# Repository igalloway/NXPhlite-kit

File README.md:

# NXPhlite-kit

*** Update - The NXPhlite kit is being made available through NXP. The ECAD files have moved to Atium and the files here are well out of date. I will leave them here for reference. Please contact NXP and ask for NXPhlite Drones and Rovers reference design information. 

This is the EAGLE-PCB based hardware board files for the initial 'lite' kit for a UAV/Multicopter.
This is Opensource hardware, using NXP Kinetis K64 and other NXP devices.

The project currently defines:
* NXPhlite-PX4 - A Flight controller board which will run PX4 software.(Similar to PIXHAWK) 
* NXPESC-UF1 - An ESC for UAVs with Field oriented Control based off NXP Kinetis KV31 or KV11.
  * Note1: We will use KV31 until KV11 is gains KMS (Kinetis Motor Suite) software support. 
  * Nate2: KV31 does not have CAN-bus but will use use similar pins as KV11. 

<br><br>

* Note that the directory <bold>NXP-Eagle-7.5.0</bold> is the EAGLE PCB directory structure. You do not have to replace your exiting EAGLE structure, but can simply add these NEW directories under "Eagle Control Panel" <options><directories>

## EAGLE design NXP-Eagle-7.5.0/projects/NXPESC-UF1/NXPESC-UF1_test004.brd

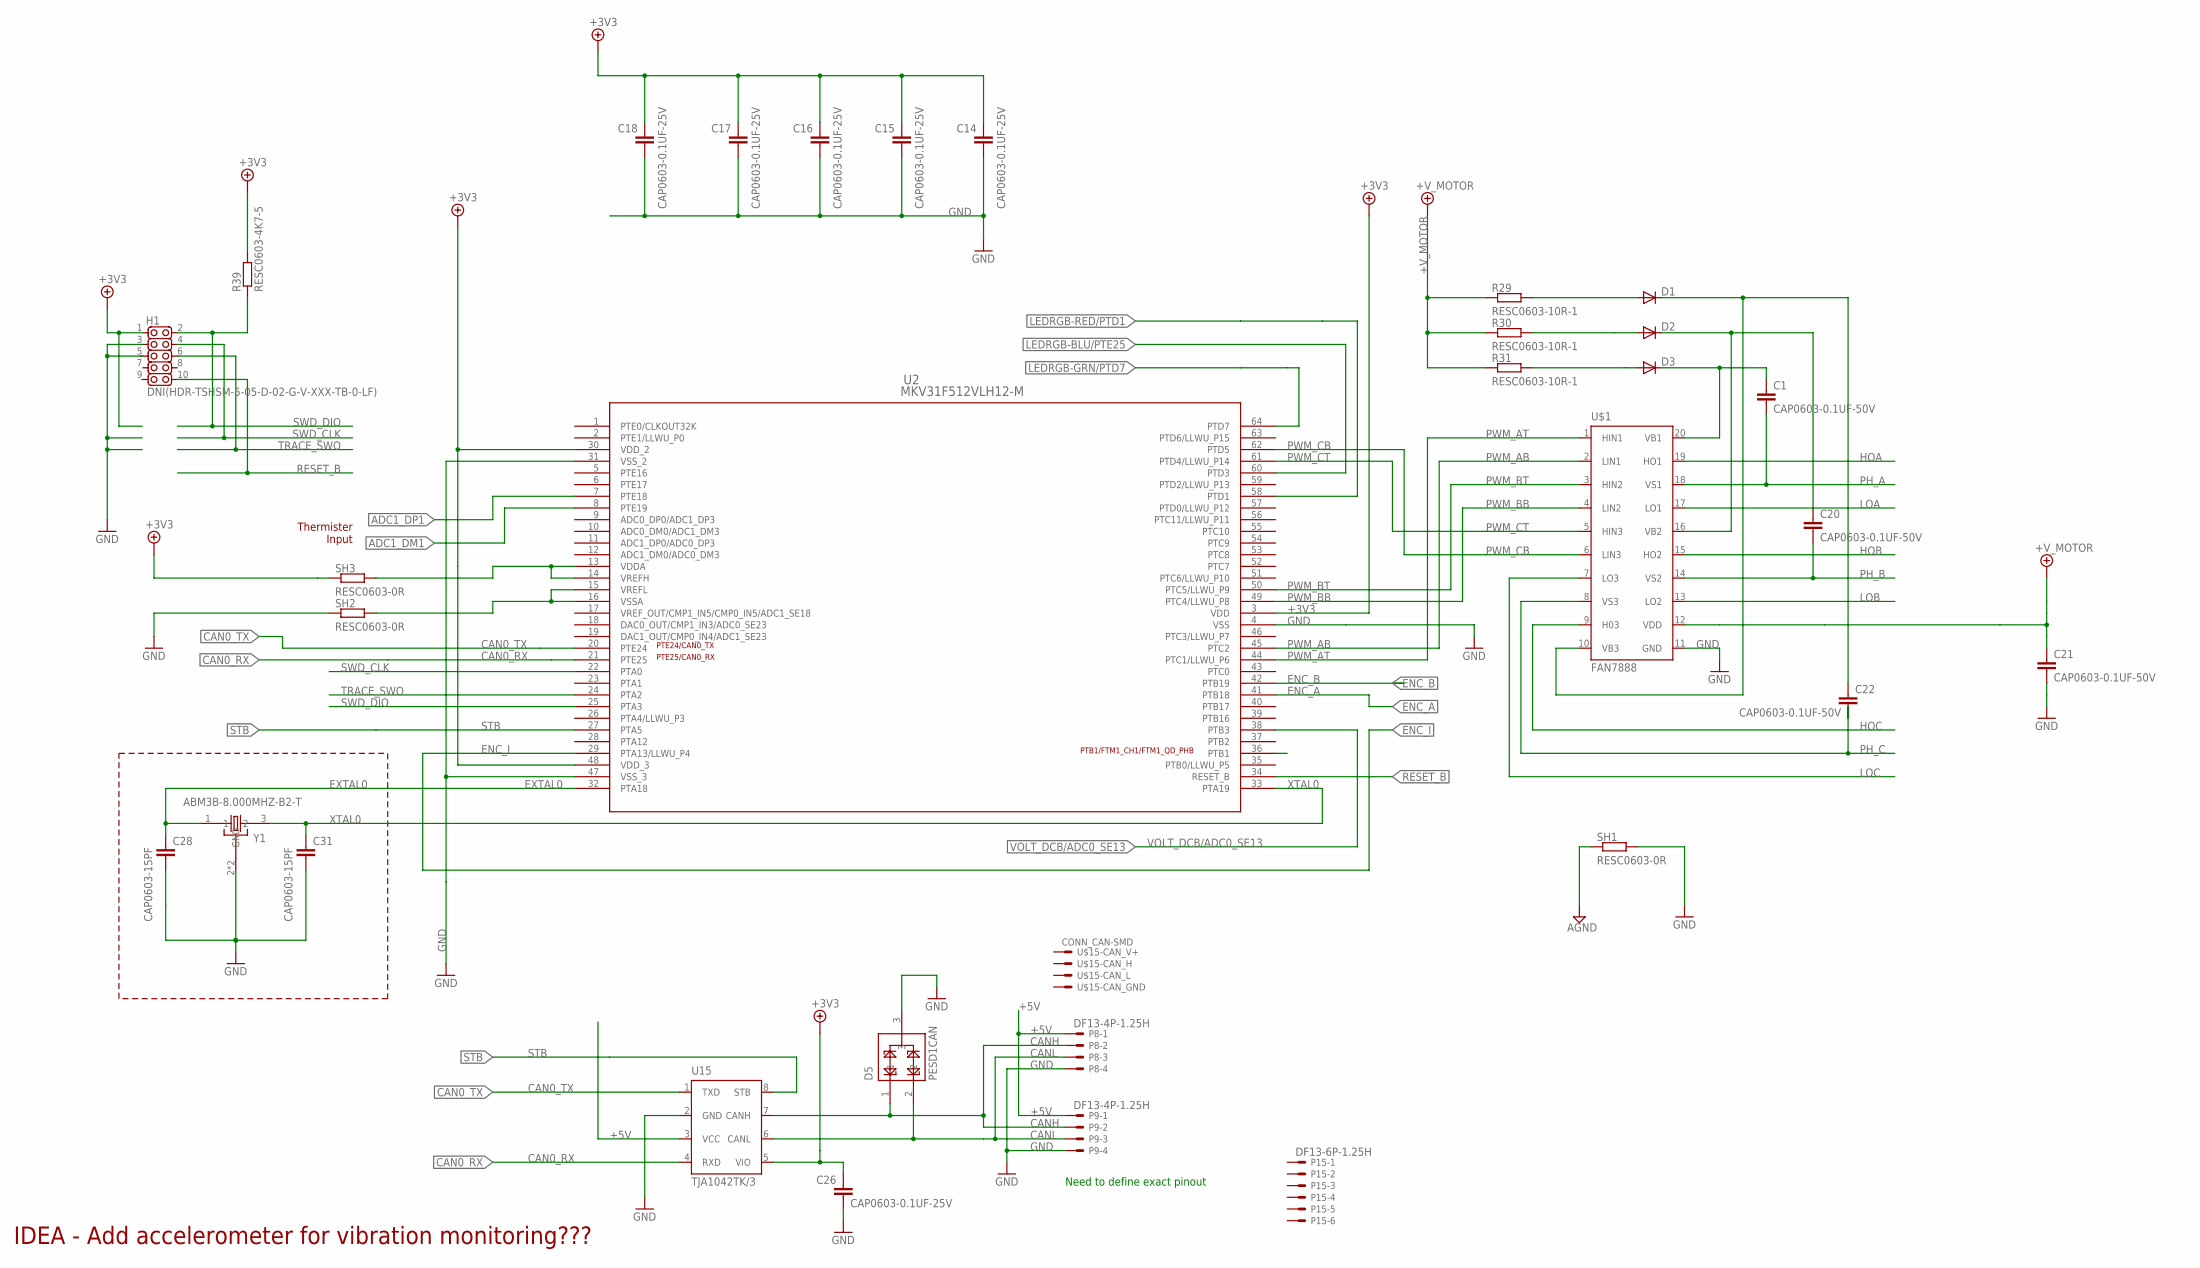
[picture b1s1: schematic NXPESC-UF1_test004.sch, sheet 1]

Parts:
C1, C20, C21, C22: CAP0603-0.1UF-50V; C0603
C14, C15, C16, C17, C18, C26: CAP0603-0.1UF-25V; C0603
C28, C31: CAP0603-15PF; C0603
D1, D2, D3: DIODE-SOD323-R; SOD323-R
D5: PESD1CAN; SOT23-3
H1: DNI(HDR-TSHSM-5-05-D-02-G-V-XXX-TB-0-LF); HD2X5-SMD-0.05"
P8, P9: DF13-4P-1.25H; DF13A-4P-1.25H
P15: DF13-6P-1.25H; DF13A-6P-1.25H
R29, R30, R31: RESC0603-10R-1; C0603
R39: RESC0603-4K7-5; C0603
SH1, SH2, SH3: RESC0603-0R; C0603
U2: MKV31F512VLH12-M; LQFP-64_10X10X1_6-M
U15: TJA1042TK/3; HVSON8
U$1: FAN7888; SOIC-20
U$15: CONN_CAN-SMD; S4B-PH-SM4-TB
Y1: ABM3B-8.000MHZ-B2-T; OSCSC500X320X110-4N

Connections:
+3V3: C14.1, C15.1, C16.1, C17.1, C18.1, C26.1, H1.1, R39.2, SH3.1, U2.3 (VDD), U2.30 (VDD_2), U2.48 (VDD_3), U15.5 (VIO); also elsewhere on the board
+5V: P8.1, P9.1, U15.3 (VCC); also elsewhere on the board
+V_MOTOR: C21.1, R29.1, R30.1, R31.1, U$1.12 (VDD); also elsewhere on the board
ADC1_DM1: U2.8 (PTE19); also elsewhere on the board
ADC1_DP1: U2.7 (PTE18); also elsewhere on the board
AGND: SH1.1; also elsewhere on the board
CAN0_RX: U2.21 (PTE25), U15.4 (RXD)
CAN0_TX: U2.20 (PTE24), U15.1 (TXD)
CANH: D5.1, P8.2, P9.2, U15.7 (CANH)
CANL: D5.2, P8.3, P9.3, U15.6 (CANL)
ENC_A: U2.41 (PTB18); also elsewhere on the board
ENC_B: U2.42 (PTB19); also elsewhere on the board
ENC_I: U2.29 (PTA13/LLWU_P4); also elsewhere on the board
EXTAL0: C28.1, U2.32 (PTA18), Y1.1
GND: C14.2, C15.2, C16.2, C17.2, C18.2, C21.2, C26.2, C28.2, C31.2, D5.3, H1.3, H1.5, P8.4, P9.4, SH1.2, SH2.1, U2.4 (VSS), U2.31 (VSS_2), U2.47 (VSS_3), U15.2 (GND), U$1.11 (GND), Y1.2 (GND), Y1.4 (GND); also elsewhere on the board
HOA: U$1.19 (HO1); also elsewhere on the board
HOB: U$1.15 (HO2); also elsewhere on the board
HOC: U$1.9 (H03); also elsewhere on the board
LEDRGB-BLU/PTE25: U2.60 (PTD3); also elsewhere on the board
LEDRGB-GRN/PTD7: U2.64 (PTD7); also elsewhere on the board
LEDRGB-RED/PTD1: U2.58 (PTD1); also elsewhere on the board
LOA: U$1.17 (LO1); also elsewhere on the board
LOB: U$1.13 (LO2); also elsewhere on the board
LOC: U$1.7 (LO3); also elsewhere on the board
unnamed: D1.A, R29.2
unnamed: D2.A, R30.2
unnamed: D3.A, R31.2
unnamed: C1.1, D3.C, U$1.20 (VB1)
unnamed: C20.1, D2.C, U$1.16 (VB2)
unnamed: C22.1, D1.C, U$1.10 (VB3)
unnamed: SH3.2, U2.13 (VDDA), U2.14 (VREFH)
unnamed: SH2.2, U2.15 (VREFL), U2.16 (VSSA)
PH_A: C1.2, U$1.18 (VS1); also elsewhere on the board
PH_B: C20.2, U$1.14 (VS2); also elsewhere on the board
PH_C: C22.2, U$1.8 (VS3); also elsewhere on the board
PWM_AB: U2.45 (PTC2), U$1.2 (LIN1)
PWM_AT: U2.44 (PTC1/LLWU_P6), U$1.1 (HIN1)
PWM_BB: U2.49 (PTC4/LLWU_P8), U$1.4 (LIN2)
PWM_BT: U2.50 (PTC5/LLWU_P9), U$1.3 (HIN2)
PWM_CB: U2.62 (PTD5), U$1.6 (LIN3)
PWM_CT: U2.61 (PTD4/LLWU_P14), U$1.5 (HIN3)
RESET_B: H1.10, U2.34 (RESET_B)
STB: U2.27 (PTA5), U15.8 (STB)
SWD_CLK: H1.4, U2.22 (PTA0)
SWD_DIO: H1.2, R39.1, U2.25 (PTA3)
TRACE_SWO: H1.6, U2.24 (PTA2)
VOLT_DCB/ADC0_SE13: U2.38 (PTB3); also elsewhere on the board
XTAL0: C31.1, U2.33 (PTA19), Y1.3 (2)

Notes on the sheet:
IDEA - Add accelerometer for vibration monitoring???
Need to define exact pinout
PTB1/FTM1_CH1/FTM1_QD_PHB
PTE24/CAN0_TX
PTE25/CAN0_RX
Thermister Input

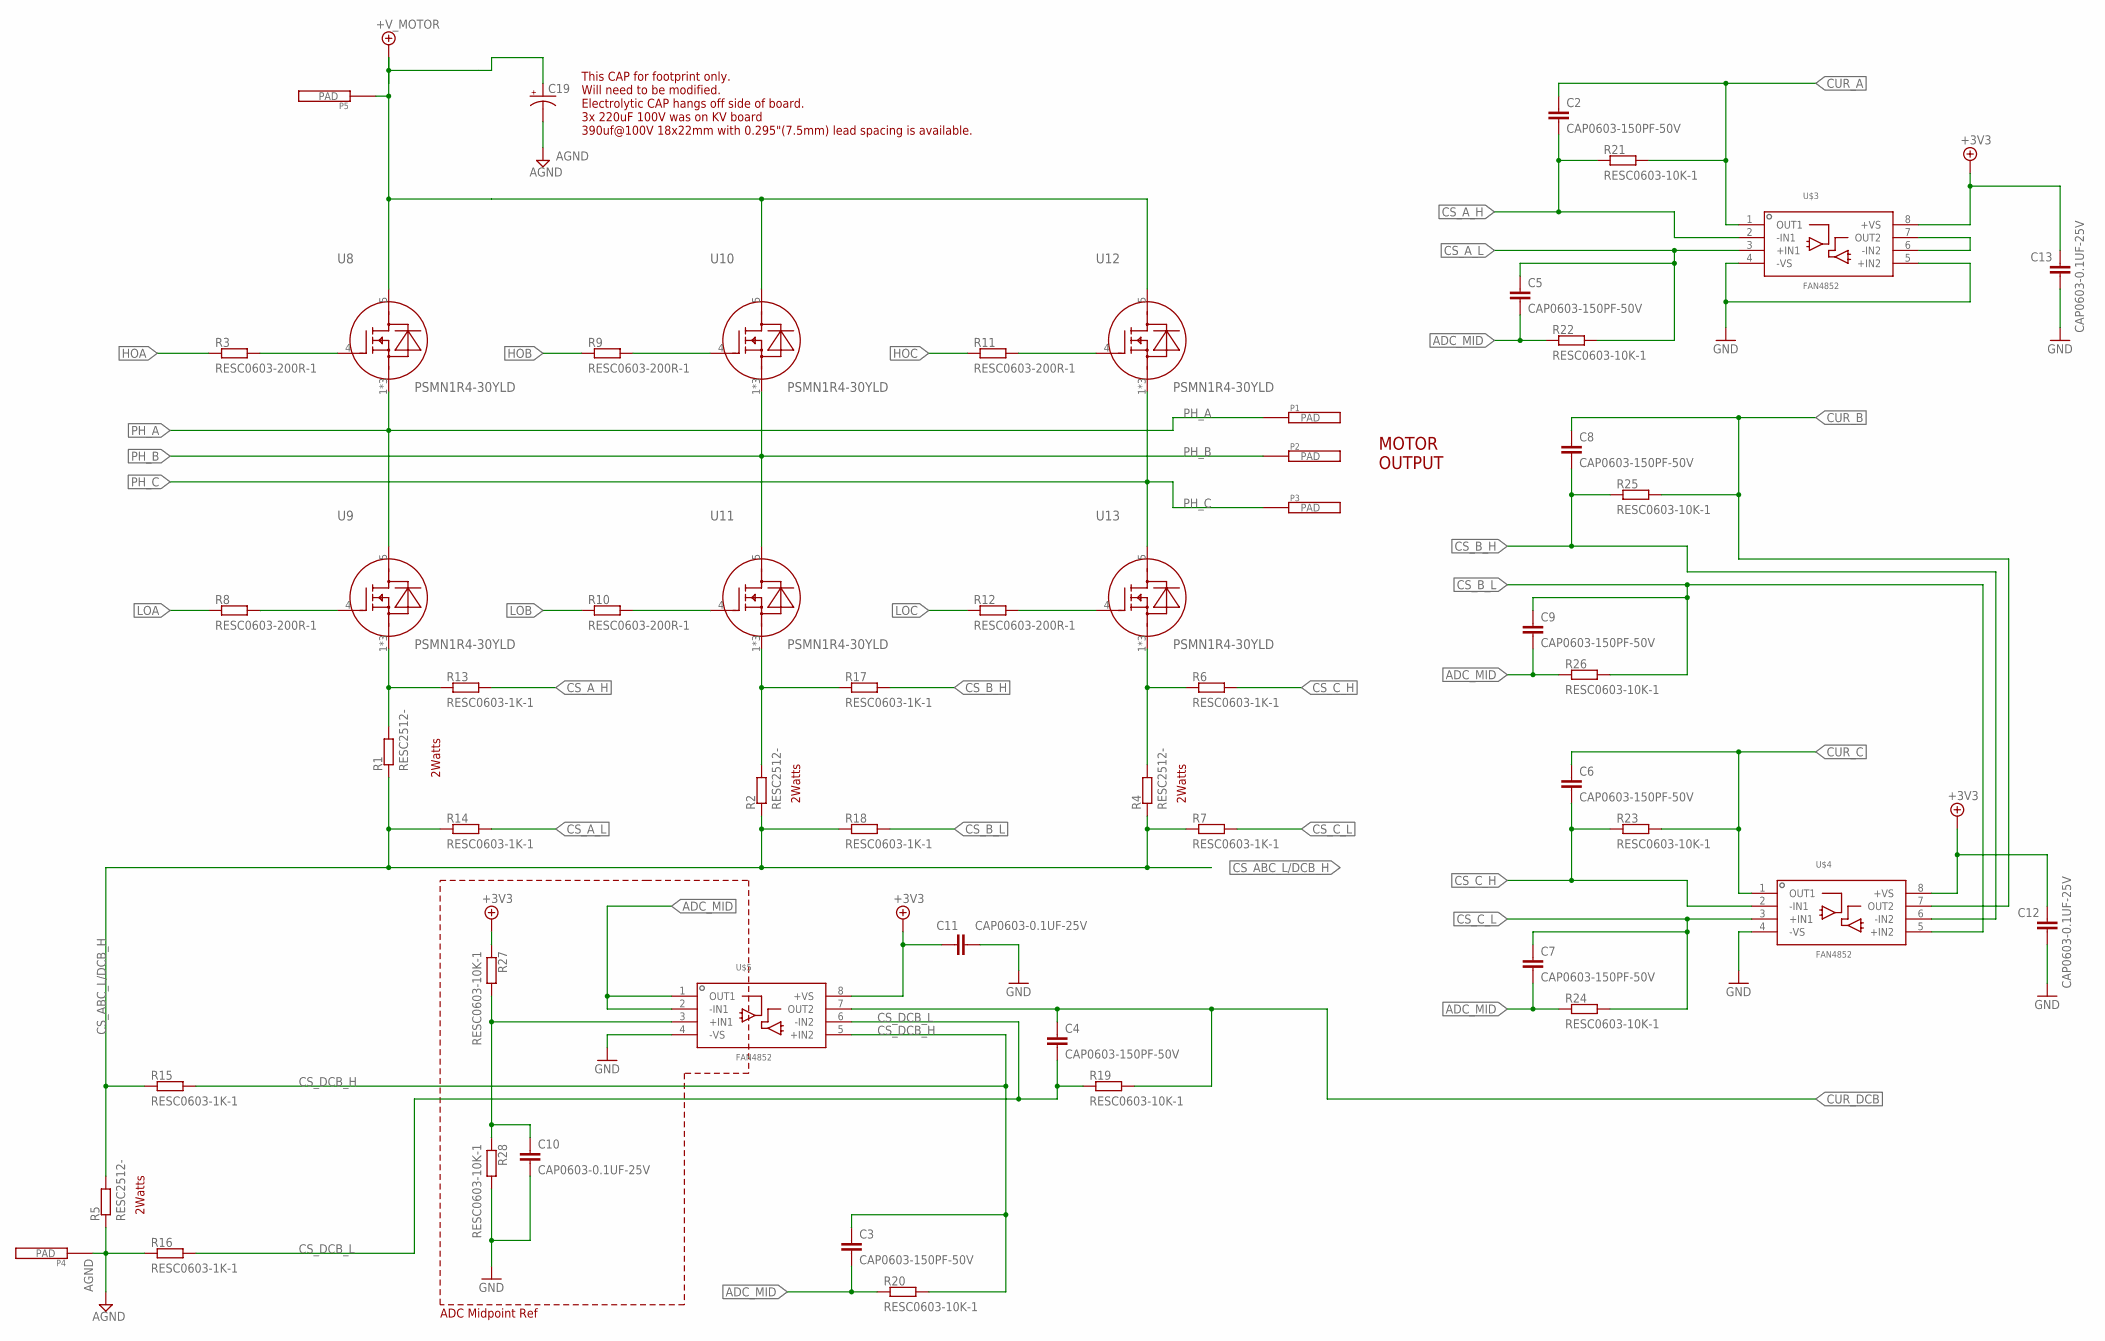
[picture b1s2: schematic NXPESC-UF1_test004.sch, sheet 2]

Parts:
C2, C3, C4, C5, C6, C7, C8, C9: CAP0603-150PF-50V; C0603
C10, C11, C12, C13: CAP0603-0.1UF-25V; C0603
C19: CPOL-USETR1; ETR1
P1, P2, P3, P4, P5: MOT_PWR_PAD-1; MPAD1
R1, R2, R4, R5: RESC2512-; R2512
R3, R8, R9, R10, R11, R12: RESC0603-200R-1; C0603
R6, R7, R13, R14, R15, R16, R17, R18: RESC0603-1K-1; C0603
R19, R20, R21, R22, R23, R24, R25, R26, R27, R28: RESC0603-10K-1; C0603
U8, U9, U10, U11, U12, U13: PSMN1R4-30YLD; LFPAK56
U$3, U$4, U$5: FAN4852; SOP65P490X110-8N

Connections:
+3V3: C11.1, C12.1, C13.1, R27.1, U$3.8 (+VS), U$4.8 (+VS), U$5.8 (+VS); also elsewhere on the board
+V_MOTOR: C19.+, P5.P$1, U8.5 (D), U10.5 (D), U12.5 (D); also elsewhere on the board
ADC_MID: C3.2, C5.2, C7.2, C9.2, R20.1, R22.1, R24.1, R26.1, U$5.1 (OUT1), U$5.2 (-IN1)
AGND: C19.-, P4.P$1, R5.1, R16.1; also elsewhere on the board
CS_ABC_L/DCB_H: R1.1, R2.1, R4.1, R5.2, R7.1, R14.1, R15.1, R18.1
CS_A_H: C2.2, R13.2, R21.1, U$3.2 (-IN1)
CS_A_L: C5.1, R14.2, R22.2, U$3.3 (+IN1)
CS_B_H: C8.2, R17.2, R25.1, U$4.6 (-IN2)
CS_B_L: C9.1, R18.2, R26.2, U$4.5 (+IN2)
CS_C_H: C6.2, R6.2, R23.1, U$4.2 (-IN1)
CS_C_L: C7.1, R7.2, R24.2, U$4.3 (+IN1)
CS_DCB_H: C3.1, R15.2, R20.2, U$5.5 (+IN2)
CS_DCB_L: C4.2, R16.2, R19.1, U$5.6 (-IN2)
CUR_A: C2.1, R21.2, U$3.1 (OUT1)
CUR_B: C8.1, R25.2, U$4.7 (OUT2)
CUR_C: C6.1, R23.2, U$4.1 (OUT1)
CUR_DCB: C4.1, R19.2, U$5.7 (OUT2)
GND: C10.2, C11.2, C12.2, C13.2, R28.2, U$3.4 (-VS), U$3.5 (+IN2), U$4.4 (-VS), U$5.4 (-VS); also elsewhere on the board
HOA: R3.1; also elsewhere on the board
HOB: R9.1; also elsewhere on the board
HOC: R11.1; also elsewhere on the board
LOA: R8.1; also elsewhere on the board
LOB: R10.1; also elsewhere on the board
LOC: R12.1; also elsewhere on the board
unnamed: R3.2, U8.4 (G)
unnamed: R1.2, R13.1, U9.1 (S), U9.2 (S), U9.3 (S)
unnamed: R8.2, U9.4 (G)
unnamed: R9.2, U10.4 (G)
unnamed: R10.2, U11.4 (G)
unnamed: R11.2, U12.4 (G)
unnamed: R2.2, R17.1, U11.1 (S), U11.2 (S), U11.3 (S)
unnamed: R4.2, R6.1, U13.1 (S), U13.2 (S), U13.3 (S)
unnamed: U$3.6 (-IN2), U$3.7 (OUT2)
unnamed: C10.1, R27.2, R28.1, U$5.3 (+IN1)
unnamed: R12.2, U13.4 (G)
PH_A: P1.P$1, U8.1 (S), U8.2 (S), U8.3 (S), U9.5 (D); also elsewhere on the board
PH_B: P2.P$1, U10.1 (S), U10.2 (S), U10.3 (S), U11.5 (D); also elsewhere on the board
PH_C: P3.P$1, U12.1 (S), U12.2 (S), U12.3 (S), U13.5 (D); also elsewhere on the board

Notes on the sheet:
MOTOR OUTPUT
2Watts
This CAP for footprint only. Will need to be modified. Electrolytic CAP hangs off side of board. 3x 220uF 100V was on KV board 390uf@100V 18x22mm with 0.295"(7.5mm) lead spacing is available.
ADC Midpoint Ref

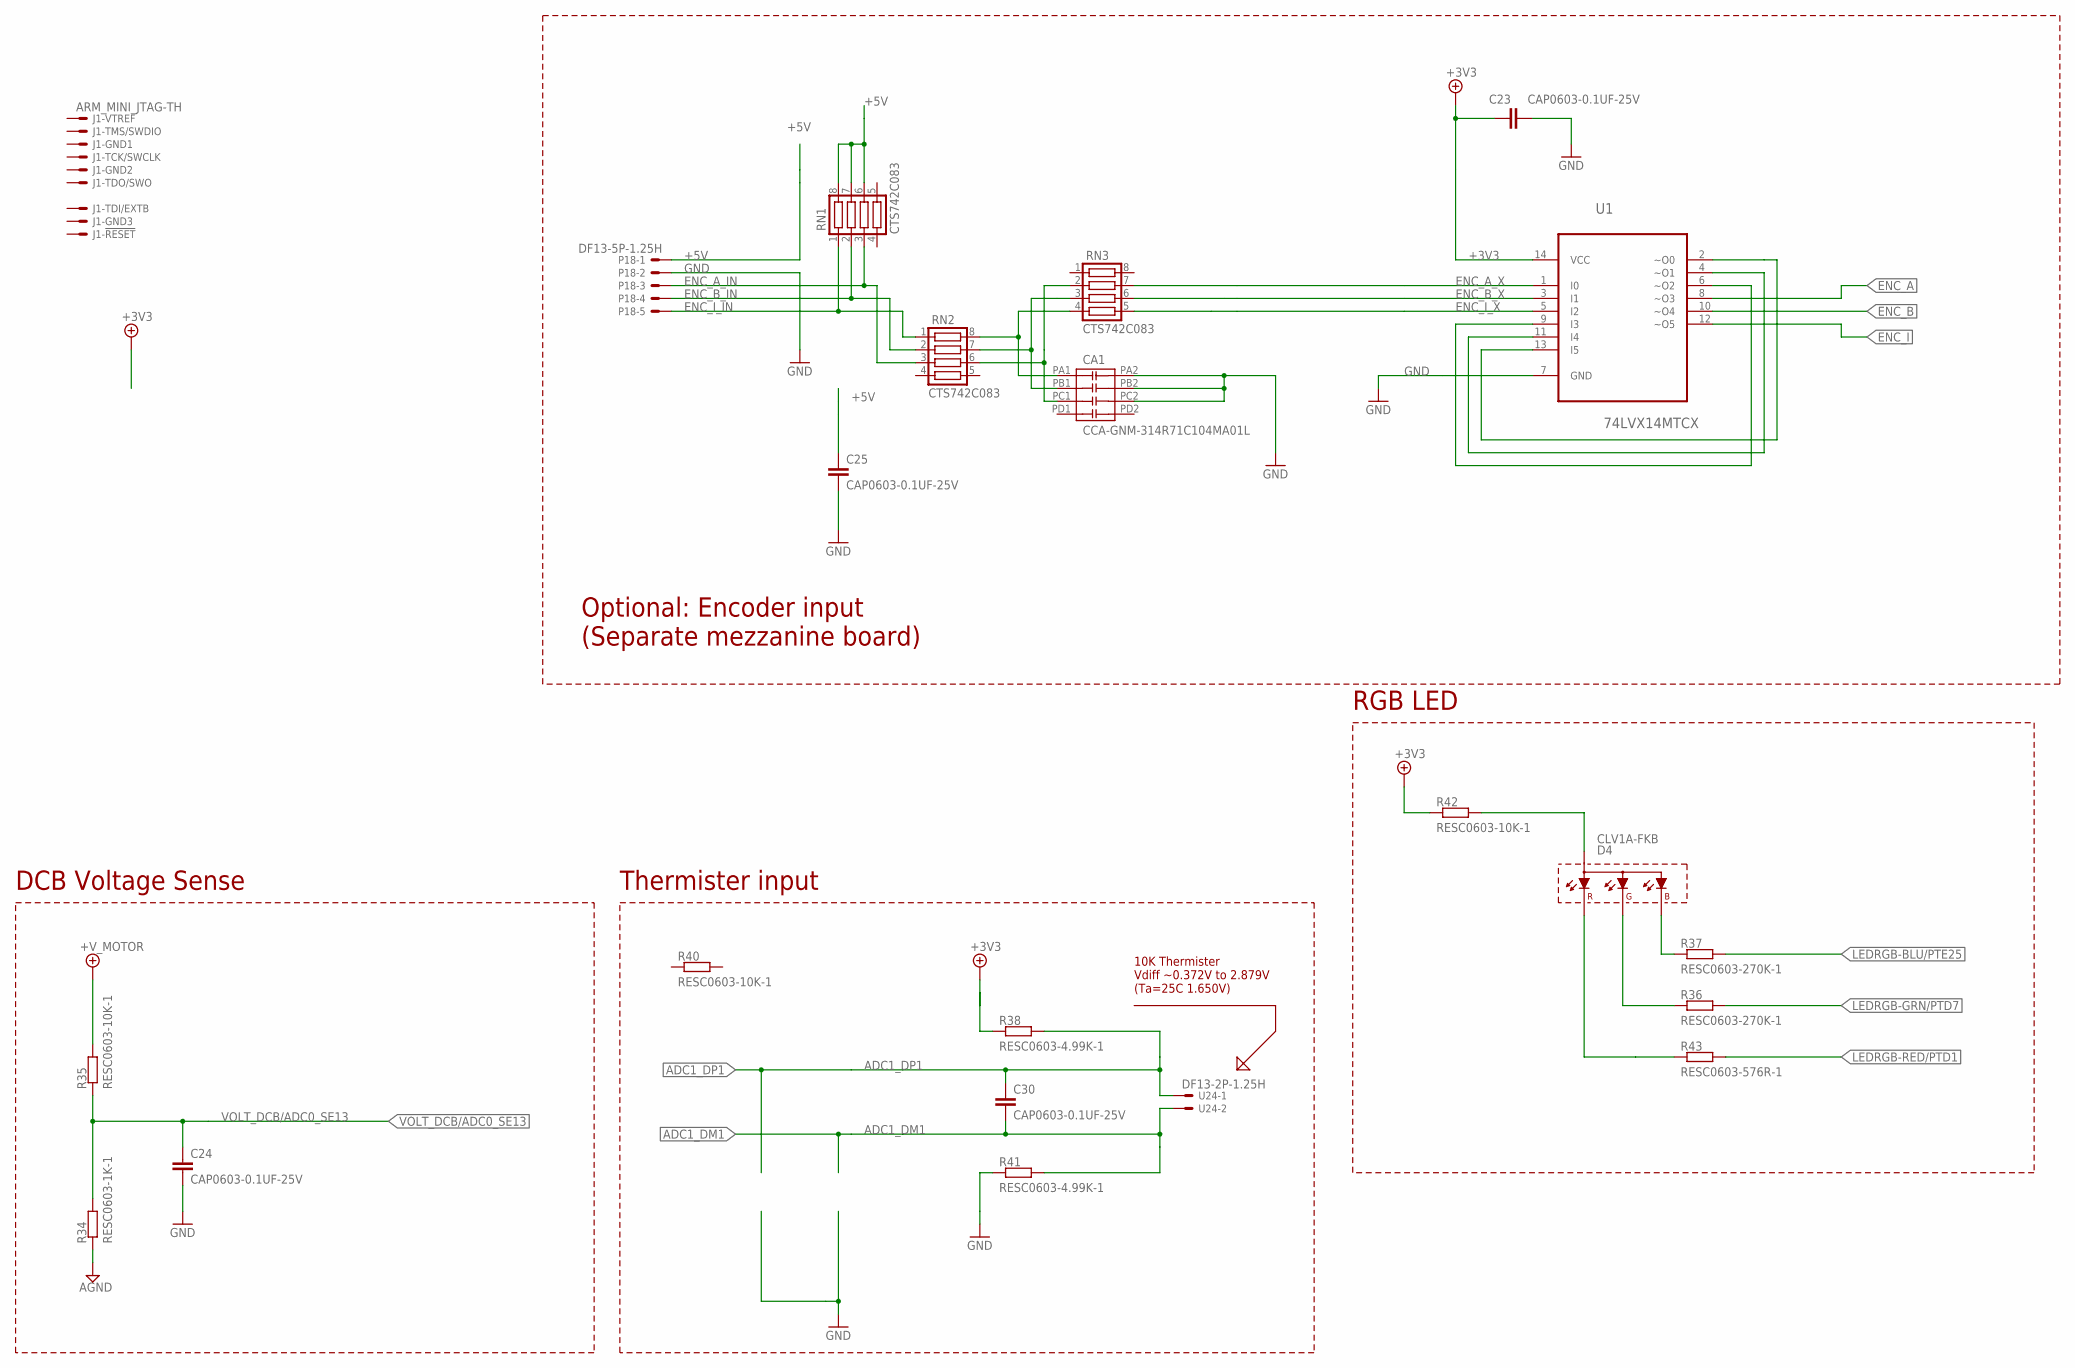
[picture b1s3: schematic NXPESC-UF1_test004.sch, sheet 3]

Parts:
C23, C24, C25, C30: CAP0603-0.1UF-25V; C0603
CA1: CCA-GNM-314R71C104MA01L; RES_ARRAY_4I_S
D4: CLV1A-FKB; 4-PLCC
J1: ARM_MINI_JTAG-TH; FTSH-105-01-XXX-DV
P18: DF13-5P-1.25H; DF13A-5P-1.25H
R34: RESC0603-1K-1; C0603
R35, R40, R42: RESC0603-10K-1; C0603
R36, R37: RESC0603-270K-1; C0603
R38, R41: RESC0603-4.99K-1; C0603
R43: RESC0603-576R-1; C0603
RN1, RN2, RN3: CTS742C083
U1: 74LVX14MTCX; SOP65P640X120-14N
U24: DF13-2P-1.25H; DF13A-2P-1.25H

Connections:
+3V3: C23.1, R38.1, R42.1, U1.14 (VCC); also elsewhere on the board
+5V: C25.1, P18.1, RN1.6, RN1.7, RN1.8; also elsewhere on the board
+V_MOTOR: R35.2; also elsewhere on the board
ADC1_DM1: C30.2, R41.2, U24.2; also elsewhere on the board
ADC1_DP1: C30.1, R38.2, U24.1; also elsewhere on the board
AGND: R34.1; also elsewhere on the board
ENC_A: U1.8 (~O3); also elsewhere on the board
ENC_A_IN: P18.3, RN1.3, RN2.3
ENC_A_X: RN3.7, U1.1 (I0)
ENC_B: U1.10 (~O4); also elsewhere on the board
ENC_B_IN: P18.4, RN1.2, RN2.2
ENC_B_X: RN3.6, U1.3 (I1)
ENC_I: U1.12 (~O5); also elsewhere on the board
ENC_I_IN: P18.5, RN1.1, RN2.1
ENC_I_X: RN3.5, U1.5 (I2)
GND: C23.2, C24.2, C25.2, CA1.PA2 (RA2), CA1.PB2 (RB2), CA1.PC2 (RC2), P18.2, R41.1, U1.7 (GND); also elsewhere on the board
LEDRGB-BLU/PTE25: R37.2; also elsewhere on the board
LEDRGB-GRN/PTD7: R36.2; also elsewhere on the board
LEDRGB-RED/PTD1: R43.2; also elsewhere on the board
unnamed: U1.2 (~O0), U1.13 (I5)
unnamed: CA1.PA1 (RA1), RN2.8, RN3.4
unnamed: CA1.PB1 (RB1), RN2.7, RN3.3
unnamed: CA1.PC1 (RC1), RN2.6, RN3.2
unnamed: U1.4 (~O1), U1.11 (I4)
unnamed: U1.6 (~O2), U1.9 (I3)
unnamed: D4.2 (A), R42.2
unnamed: D4.3 (CBLUE), R37.1
unnamed: D4.4 (CGREEN), R36.1
unnamed: D4.1 (CRED), R43.1
VOLT_DCB/ADC0_SE13: C24.1, R34.2, R35.1; also elsewhere on the board

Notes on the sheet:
DCB Voltage Sense
Optional: Encoder input (Separate mezzanine board)
Thermister input
RGB LED
10K Thermister Vdiff ~0.372V to 2.879V (Ta=25C 1.650V)

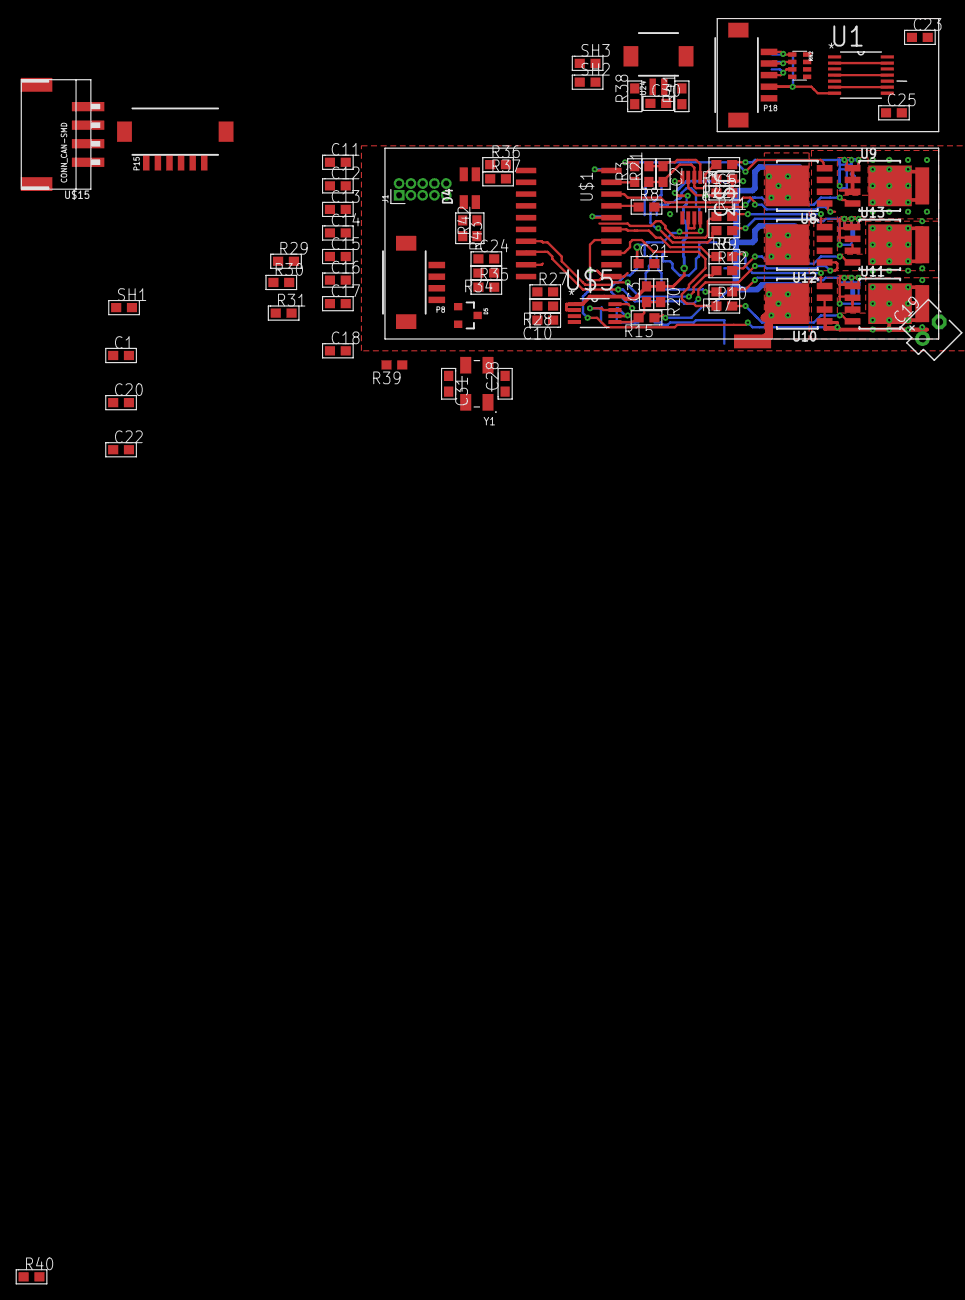
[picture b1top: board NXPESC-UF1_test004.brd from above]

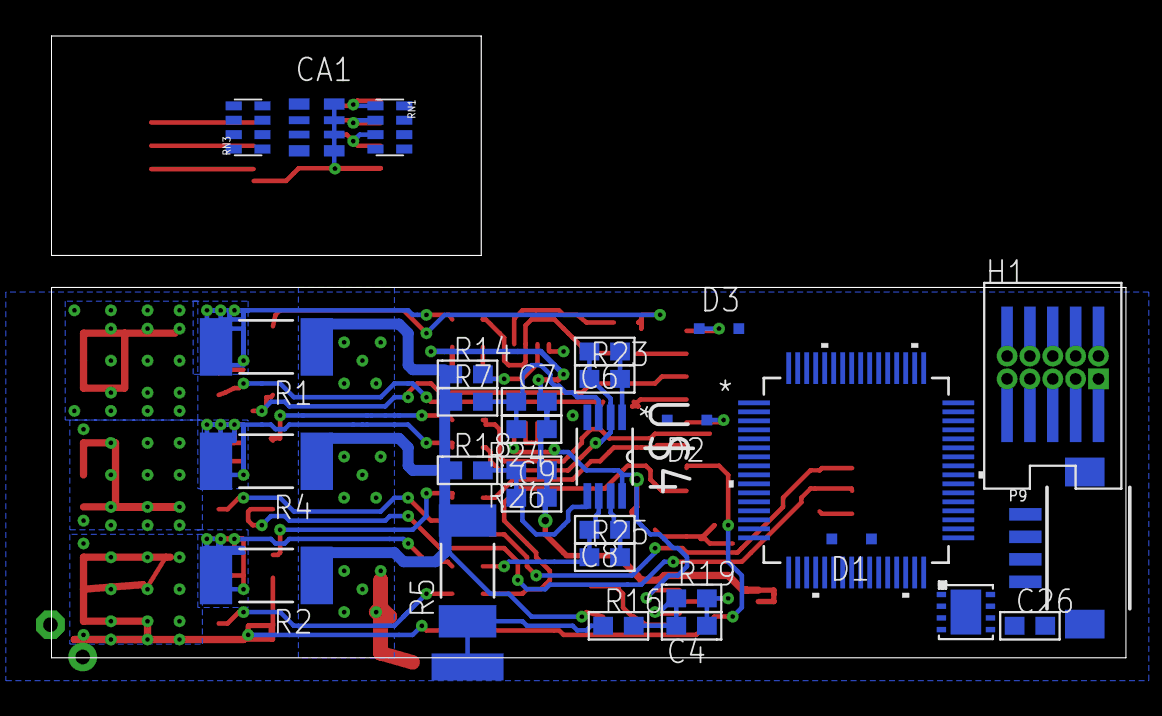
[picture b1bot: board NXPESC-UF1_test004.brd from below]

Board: 2 copper layers, 59.7 x 34.5 mm, 109 parts (31 on the bottom side), 89 nets.

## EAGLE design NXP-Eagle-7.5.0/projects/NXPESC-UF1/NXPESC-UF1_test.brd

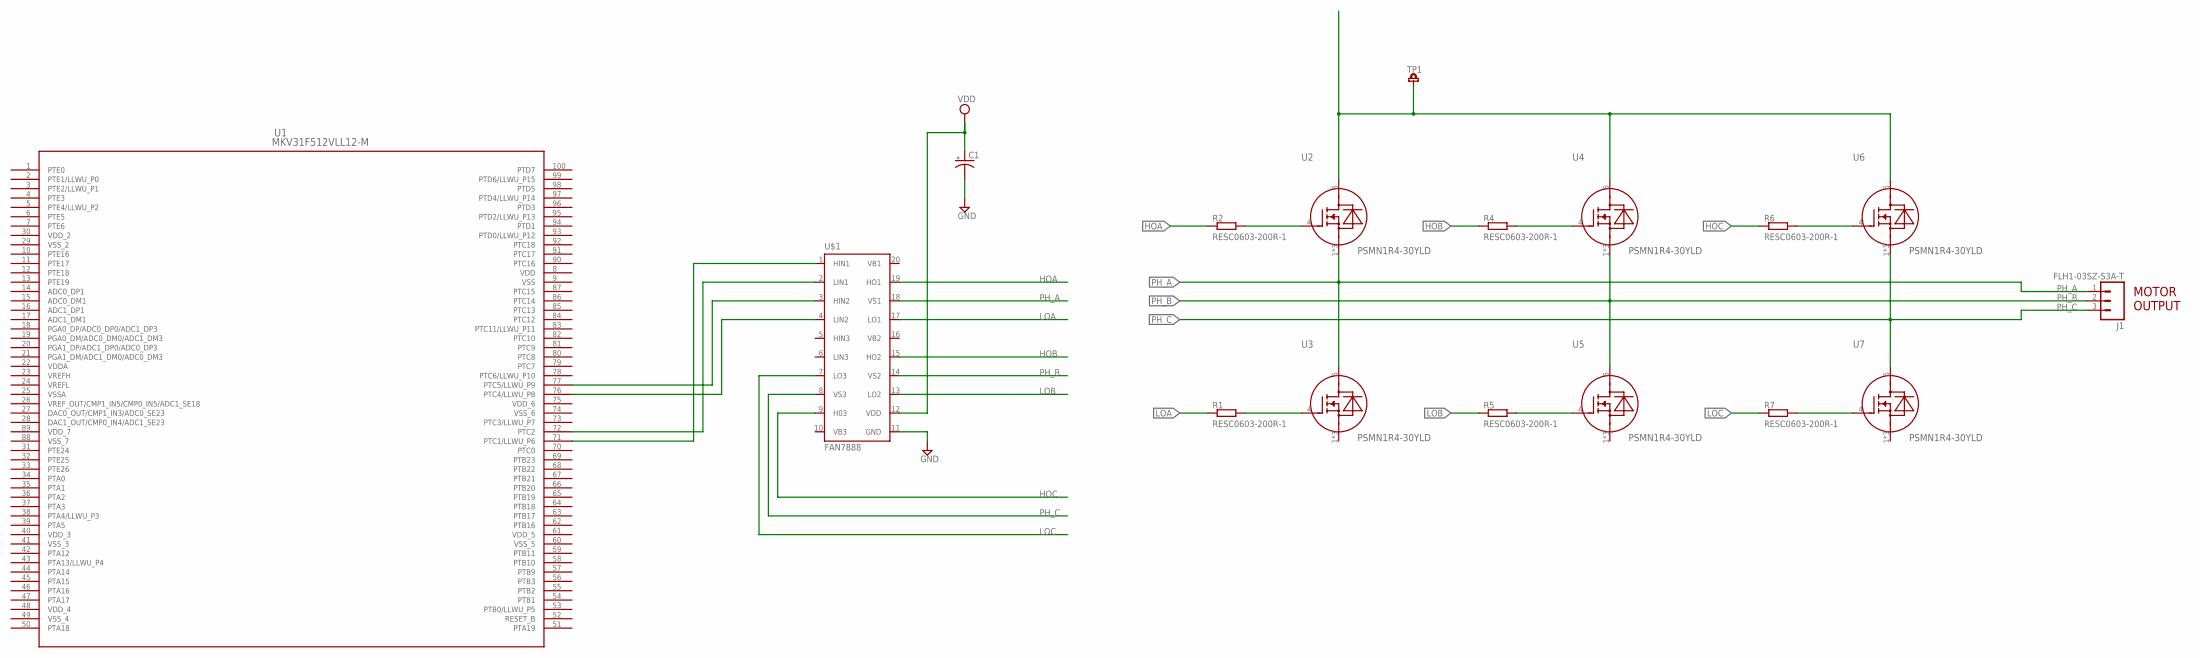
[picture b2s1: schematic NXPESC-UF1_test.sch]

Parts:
C1: CAP_POL1206; EIA3216
J1: FLH1-03SZ-S3A-T; J3
R1, R2, R4, R5, R6, R7: RESC0603-200R-1; C0603
TP1: TP-TH-SMLL; TP-SMLL
U1: MKV31F512VLL12-M; LQFP-100_14X14X1_7-M
U2, U3, U4, U5, U6, U7: PSMN1R4-30YLD; LFPAK56
U$1: FAN7888; SOIC-20

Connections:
GND: C1.C (-), U$1.11 (GND)
HOA: R2.1, U$1.19 (HO1)
HOB: R4.1, U$1.15 (HO2)
HOC: R6.1, U$1.9 (H03)
LOA: R1.1, U$1.17 (LO1)
LOB: R5.1, U$1.13 (LO2)
LOC: R7.1, U$1.7 (LO3)
unnamed: TP1.1, U2.5 (D), U4.5 (D), U6.5 (D)
unnamed: U1.71 (PTC1/LLWU_P6), U$1.1 (HIN1)
unnamed: U1.72 (PTC2), U$1.2 (LIN1)
unnamed: U1.77 (PTC5/LLWU_P9), U$1.3 (HIN2)
unnamed: U1.76 (PTC4/LLWU_P8), U$1.4 (LIN2)
unnamed: R2.2, U2.4 (G)
unnamed: R1.2, U3.4 (G)
unnamed: R4.2, U4.4 (G)
unnamed: R5.2, U5.4 (G)
unnamed: R6.2, U6.4 (G)
unnamed: R7.2, U7.4 (G)
PH_A: J1.1, U2.1 (S), U2.2 (S), U2.3 (S), U3.5 (D), U$1.18 (VS1)
PH_B: J1.2, U4.1 (S), U4.2 (S), U4.3 (S), U5.5 (D), U$1.14 (VS2)
PH_C: J1.3, U6.1 (S), U6.2 (S), U6.3 (S), U7.5 (D), U$1.8 (VS3)
VB1: U$1.20 (VB1)
VB2: U$1.16 (VB2)
VB3: U$1.10 (VB3)
VDD: C1.A (+), U1.8 (VDD), U$1.12 (VDD)
VDDA: U1.22 (VDDA)
VDD_2: U1.30 (VDD_2)
VDD_3: U1.40 (VDD_3)
VDD_4: U1.48 (VDD_4)
VDD_5: U1.61 (VDD_5)
VDD_6: U1.75 (VDD_6)
VDD_7: U1.89 (VDD_7)
VREFH: U1.23 (VREFH)
VREFL: U1.24 (VREFL)
VSS: U1.9 (VSS)
VSSA: U1.25 (VSSA)
VSS_2: U1.29 (VSS_2)
VSS_3: U1.41 (VSS_3)
VSS_4: U1.49 (VSS_4)
VSS_5: U1.60 (VSS_5)
VSS_6: U1.74 (VSS_6)
VSS_7: U1.88 (VSS_7)

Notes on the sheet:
MOTOR OUTPUT

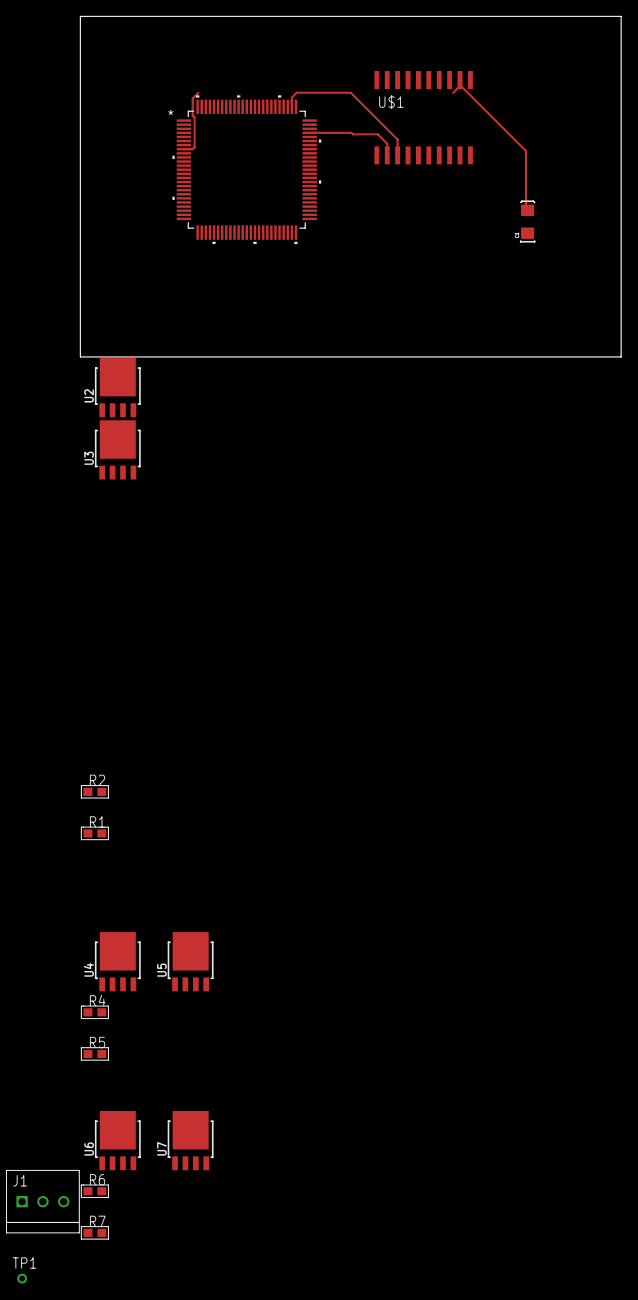
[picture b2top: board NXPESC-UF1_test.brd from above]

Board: 2 copper layers, 66.0 x 41.6 mm, 17 parts (0 on the bottom side), 22 nets.

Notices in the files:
NXP-Eagle-7.5.0/projects/examples/ti-launchpad/MSP-EXP430F5529LP.brd:
(C)2003 A. DANNENBERG
parts and their libraries:
NXPHLITE: Copyright (c) 2017 xxxxxx
moudle-new: This work is licensed under the Creative Commons Attribution 4.0 International License.
To view a copy of this license,visit:
http://creativecommons.org/licenses/by-sa/4.0
moudle-new: CC-BY-SA
